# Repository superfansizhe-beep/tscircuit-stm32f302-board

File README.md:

# STM32F302R8T6 考核板 —— 用 TypeScript 画电路

**这是一块完整的 STM32 开发板的全部设计源文件**：原理图、PCB、BOM、
交付产物，以及把 tscircuit（电路即代码）跑起来的钉死工具链。

| | |
|---|---|
| 板子 | **80 × 80 mm，4 层** |
| 主控 | STM32F302R8T6（LQFP-64） |
| 元件 | 84 个（261 SMT 焊盘 + 76 通孔） |
| 原理图 | **9 页**（电源 / 最小系统 / 串口 / I2C / SPI / CAN / PWM / ADC / 指示灯） |
| 走线 | 234 条、197 个过孔 |
| 铜皮 | 内层1 + 底层 GND 平面 |

## 这块板做什么

一块自制的 STM32F302 开发板，把常用外设一次性做全：

- **电源**：XT30 输入 → 拨动开关 → RY8411 降压到 5V → TLV75733 LDO 到 3.3V，三颗电源指示灯
- **最小系统**：8MHz HSE 晶振、复位/启动按键、SWD 调试口、全套去耦
- **外设**：3 路串口（PH2.0）、3 路 I2C（EEPROM + 温度传感器 + 引出）、
  2 路 SPI（MCP23S17 扩 16 路 GPIO + 引出）、1 路 CAN、
  6 路 PWM 舵机轨、3 路 ADC 电源电压采样、3 路 GPIO 指示灯

## 交付产物在哪

[`out/stm32f302/deliverables/`](out/stm32f302/deliverables/) ——
**含 `.epro2` 转换步骤与已知问题，要交作业先看这里的说明。**

| 目录 | 内容 |
|------|------|
| `01-原理图/` | 九页 PDF + 分页 PNG + 矢量 SVG |
| `02-PCB/` | 正反面/全板图 + Gerber（4 层，含内层与钻孔） |
| `03-导入EasyEDA/` | Altium 工程（转 `.epro2` 用）+ KiCad PCB |
| `04-制造资料/` | BOM.csv（37 种料号）+ 网表 |
| `05-3D/` | 整板 STEP 模型 |

## 为什么"电路是代码"

整块板用 TSX 描述（`<chip>` `<resistor>` `<trace>` 这些标签），
而不是画在 EDA 软件里。好处是**可复跑、可 diff、可程序化校验**：

```bash
export PATH="$HOME/Desktop/tscircuit/.tooling/bun/bin:$PATH"
./tsci-run export circuits/stm32f302/main.tsx -f circuit-json -o ../../out/stm32f302/main.json

python3 scripts/check-modules.py   # 元件数 / 丢件 / 几何重叠 / 越出板边
python3 scripts/erc.py             # 八项电气规则（短路 / 重复网络 / 悬空脚 …）
./scripts/render-all.sh            # 刷新全部图片
./scripts/export-deliverables.sh   # 刷新全部交付文件
python3 scripts/gen-bom.py         # 从电路产物反推 BOM
```

**这两个校验脚本不是摆设** —— 它们在开发过程中抓出了 8 个"构建成功但板子是废的"
的错误，比如：晶振缺参数导致元件静默消失、绿/蓝 LED 极性写反、
磁珠料号在库里不存在导致元件零焊盘、网络名与位号重名等等。
逐条记录在 [`circuits/stm32f302/README.md`](circuits/stm32f302/README.md)。

## 目录

| 路径 | 说明 |
|------|------|
| `circuits/stm32f302/` | **本项目**：9 个模块 + 零件库 + 需求/引脚/BOM/位号文档 |
| `circuits/stm32f302/parts/` | 可复用零件（降压块、LDO 块、指示灯、PH2.0 接口、上拉对、分压） |
| `scripts/` | 验收、ERC、BOM 生成、渲染、导出 |
| `out/stm32f302/` | 构建产物与交付文件 |
| 以下 | 宿主环境的工具链契约 |

---

# my-tscircuit —— 基准机 / 环境契约

这是**基准机**，不是 mock。它是钉死的、可复跑的宿主环境：正式的电路项目也住在这里面，
或者整个目录复制一份当模板用。

**环境不可变，复现靠目录快照，而不是靠记忆。**

> 本文档里的命令都是在本目录实测跑出来的，不是照抄文档。
> 标 ⚠️ 的是实测踩到、且和原始契约写法**不一致**的地方。

---

## Toolchain Contract

| # | 契约 | 内容 |
|---|------|------|
| 1 | 运行时 | Bun 1.3.3。用 `tsci-run` wrapper 起；Node 跑会报 `ERR_UNSUPPORTED_DIR_IMPORT`（Node 不允许目录 import，Bun 允许） |
| 2 | 包 | `@tscircuit/cli@0.1.2277` + `tscircuit@0.0.2790`；`package.json` 的 `overrides` 钉死 `@tscircuit/core@0.0.2119` |
| 3 | 源 | `.npmrc` 指 `registry=https://registry.npmjs.org`（npmmirror 同步滞后，取不到钉死版本） |
| 4 | 网络 | `kicad:` / `jlcpcb:` 封装抓取走本地 gost 中继 `127.0.0.1:8118`，由 `bunfig.toml` 的 `preload` wrap `fetch` 注入 |
| 5 | fd | `tsci dev` 需要 > 2048（`ulimit -n 65536`）；沙箱硬顶 2048 时 fallback 到无头 `export` |
| 6 | 补丁 | `patches/@tscircuit%2Fcore@0.0.2119.patch` 由 `bun install` 自动应用，把 core#4481 的诊断修复固化下来（见「本地补丁」） |

### 为什么必须是这个目录，不能全局装

契约里有 4 条只在项目目录内才生效：

| 契约 | 全局做不了的原因 |
|------|------------------|
| `overrides` 钉 core 版本 | `package.json` overrides 是项目级机制，全局装包没法 override 别的包的依赖树 |
| `.npmrc` 指官方源 | 可以全局，但项目级更稳，不受你机器上其他项目切换源影响 |
| `bunfig.toml` preload wrap fetch | preload 配置按项目目录读，只有在这里跑的 bun 命令会加载它 |
| `node_modules` 隔离 | Bun 目录 import 风格的 ESM 只在这个 node_modules 里自洽，扔别的目录下 Node 会炸 |

所以「新文件夹」不是习惯，是这些钉子的唯一挂载点。

### 版本钉子的真实依据

- `@tscircuit/cli@0.1.2277` 本身是**零依赖打包**（`bin: tscircuit-cli`），不直接吃 core；
  真正吃 core 的是 `tscircuit@0.0.2790`，它声明 `@tscircuit/core: ^0.0.2117`。
  caret 会浮动，所以用 `overrides` 钉到具体版本 `0.0.2119`（该包当前的 latest）。
  实测装出来确实是 `0.0.2119`。
- 这类「Cannot find module '@tscircuit/core'」的报错在 tscircuit/cli 的 issue
  #1657 / #3982 有复现（不同 core 版本组合），钉版本是标准解法。
- `ERR_UNSUPPORTED_DIR_IMPORT` 是 Node 的 ESM 目录导入错误，Bun 默认允许 —— 第 1 条契约的由来。

---

## ⚠️ 三处必须偏离原始写法的地方

### 1. 不要用 `bunx --bun @tscircuit/cli`

```bash
# ❌ 不要这样 —— 实测会打印 "Resolved, downloaded and extracted [618]"
bunx --bun @tscircuit/cli export circuits/blink.tsx -f pcb-svg
```

`bunx` 在自己的临时缓存目录里**重新解析整棵依赖树**，完全绕开本项目的
`node_modules` 和 `package.json` 的 `overrides` —— 等于把**第 2 条契约直接作废**，
还会重新触发 sharp 的 install script。

### 2. 也不要直接跑 `node_modules/.bin/tscircuit-cli`

```bash
# ❌ 不要这样
./node_modules/.bin/tscircuit-cli export ...
```

它的 shebang 是 `#!/usr/bin/env node`，直接执行就落到 Node 上 → `ERR_UNSUPPORTED_DIR_IMPORT`。

所以才有 `tsci-run`：它用 `process.execPath`（Bun 自身绝对路径）强制 Bun 运行时，
同时指向**本地那份**钉死的 CLI。两个问题一次解决。

### 3. `-o` 是文件路径，且相对**电路文件所在目录**解析

```bash
# ❌ 会被解析成 circuits/out/ → ENOENT
./tsci-run export circuits/blink.tsx -f pcb-svg -o out/blink.svg

# ✅ 对
./tsci-run export circuits/blink.tsx -f pcb-svg -o ../out/blink.pcb.svg
```

`-o` 要给完整文件名，不能给目录。

---

## 常用命令（已验证可跑）

```bash
cd my-tscircuit

# ⚠️ 必须带 --ignore-scripts
# 实测：不带会因 sharp 的 postinstall 失败而返回非零退出码（CI / set -e 会直接中断）。
# 带了就干净通过（rc=0），且 5 种导出格式与版本钉死全部正常 —— sharp 在本项目里根本用不到。
bun install --frozen-lockfile --ignore-scripts
```

**导出（无头，一次性产物，fd 受限时的 fallback）**

```bash
./tsci-run export circuits/blink.tsx -f readable-netlist -o ../out/blink.netlist.txt
./tsci-run export circuits/blink.tsx -f pcb-svg        -o ../out/blink.pcb.svg
./tsci-run export circuits/blink.tsx -f schematic-svg  -o ../out/blink.schematic.svg
./tsci-run export circuits/blink.tsx -f pcb-png        -o ../out/blink.pcb.png
./tsci-run export circuits/blink.tsx -f gerbers        -o ../out/blink.gerbers.zip
```

实测全部通过。`export --help` 里支持的格式还有：
`json` `circuit-json` `schematic-pdf` `gltf` `glb` `specctra-dsn` `kicad_sch`
`kicad_pcb` `kicad_zip` `altium` `kicad-library` `srj` `step` `assembly-svg`
`component-box-3mf`

**开发服务器（需要 watch + 多 worker，fd 消耗大）**

```bash
ulimit -n 65536                              # macOS 默认偏低，先抬 fd
./tsci-run dev circuits/blink.tsx            # → http://localhost:3020
```

实测 `lsof` 确认监听 `*:3020`，`curl` 返回 200。

`fd` 不够时的取舍：dev 起多 worker + watch，吃 fd；export 是无头单次任务，不受影响。
沙箱 fd 硬顶 2048 时一律退回 export。

---

## 已知问题（不阻塞，但要知道）

### sharp 的 postinstall 会失败 —— 已绕过，不影响任何导出

`sharp@0.32.6` 要从 GitHub release 拉 libvips 预编译包，本机网络拉不下来
（HTTP/2 framing error / ECONNREFUSED / timeout 都遇到过），fallback 去源码编译也失败，
最终 `install script from "sharp" exited with 1`。

**实测影响**：
- `require("sharp")` 会抛「Cannot find module sharp-darwin-arm64v8.node」
- 但 **svg / png / gerbers / netlist 五种导出全部照常**（`pcb-png` 走 resvg，不经 sharp）
- 唯一实际后果：`bun install` 返回**非零退出码**，CI 或 `set -e` 会中断

**已修**：安装命令统一带 `--ignore-scripts`（见「常用命令」），rc=0，且导出全绿。
本项目任何路径都用不到 sharp，跳过所有 install script 是安全的。
真要用 sharp 时再单独 `cd node_modules/sharp && node install/libvips`（前提是网络能通）。

### `-f circuit-json` 会写两份文件

实测：对 `circuits/blink.tsx` 跑 `-f circuit-json -o ../out/check.json`，
除了 `out/check.json`，**还会在电路文件旁多写一份 `circuits/blink.circuit.json`**，
两份内容逐字节相同。

不影响正确性，但会污染源码目录。已在 `.gitignore` 里排除 `circuits/*.circuit.json`。
其他格式（netlist / svg / png / gerbers）实测**不会**有这个问题。

### autorouting 产物存不下来 —— 上游问题，已提 issue + PR

`@tscircuit/core@0.0.2119`（截至 2026-10-09 的 npm latest）会出现：

```
Could not save autorouting paths for subcircuit_source_group_0:
Saved phase path ".LED1 > port.pin1" must end at another connection endpoint;
use autorouter="fanout" for saved escapes
```

**注意：PCB 本身是正确布线的**（无 `pcb_autorouting_error`，`pcb_trace` 都有真实几何和
正确的起止 `pcb_port_id`）。丢的只是 `.tscircuit/autorouting-artifacts/` 那个
可回放产物，CLI 因此跳过写入。严重性：**轻微**，不是渲染缺陷。

**真实根因**（在 core 仓库里逐变量插桩定位到的，比最初的猜测更窄）：saved path 要求
走线两端属于**同一条 SRJ 连接**；而当某个 pin 同时属于两条连接时，路由器会把这条网络
布成一棵**跨连接**的树——经由另一条连接的 port 抵达，而不是直接连线过去。此时无论
锚在哪一端都无法表达，该产物只能作废。

`autorouter="fanout"`（报错自己推荐的解法）实测**一字不变地无效**。

最小复现（`R1.pin2` 同时属于两条连接）：

```tsx
<chip name="U1" footprint="soic8" pinLabels={{ pin1: "VCC", pin2: "GND", pin3: "OUT", pin4: "IN" }} pcbX={0} />
<resistor name="R1" resistance="330" footprint="0402" pcbX={-6} pcbY={0} />
<led name="LED1" footprint="0402" pcbX={6} pcbY={0} />
<trace from="U1.VCC" to="R1.pin1" />
<trace from="U1.OUT" to="R1.pin2" />
<trace from="R1.pin2" to="LED1.pin1" />
<trace from="LED1.pin2" to="U1.GND" />
```

**影响**：`circuits/blink.tsx` 恰好有一个 pin（`R1.pin2`）同时属于两条连接，所以踩到了；
改成串联通路就不会出现。导出本身永远成功，只是那个产物存不下来。

### 相关上游进展（2026-10-09 查）

**已提交**：[issue #4481](https://github.com/tscircuit/core/issues/4481)（已按实测更正根因与严重性）
+ [PR #4482](https://github.com/tscircuit/core/pull/4482) —— 修的是**报错误导性**：
在锚定走线时识别「跨连接」形态，用可读的 port 名报出是哪两个 port，
不再甩锅给一条从未被保存的路径、不再推荐无效的 `autorouter="fanout"`。
（+37 行、0 删除，带 `tests/repros/` 复现测试与 PCB 快照，在 main 上红、修复后绿。）

| 编号 | 状态 | 说明 |
|------|------|------|
| [core#4482](https://github.com/tscircuit/core/pull/4482) | **open（本次提交）** | 让诊断指向真实成因 |
| [core#4481](https://github.com/tscircuit/core/issues/4481) | open（本次提交） | 问题报告，含最小复现与隔离表 |
| [core#4197](https://github.com/tscircuit/core/issues/4197) | 已关闭 | 同一句报错的出处，由 [#4204](https://github.com/tscircuit/core/pull/4204) 修复且**确实包含在 0.0.2119 里**（compare `7f68819...abe48513` = ahead 239 / behind 0）。但本条是**另一个成因**（跨连接走线），不是那个修复的残留缺口 |
| [core#3887](https://github.com/tscircuit/core/issues/3887) | 已关闭 | 症状同为 `undefined connectedPort.x`，但触发条件是**异步/文件加载的 `.kicad_mod` 封装**缺 `pcb_port_id`，由 #3889/#3892 修复。与本条不是同一路径 |
| [core#4337](https://github.com/tscircuit/core/pull/4337) | open | repro：对角封装铜箔 abort autorouting。相邻但不同 |
| [core#4477](https://github.com/tscircuit/core/pull/4477) | open | fix：保留手动 `pcbPath`。相邻但不同 |
| [core#4192](https://github.com/tscircuit/core/pull/4192) | open | fix：忽略无主顶层走线。相邻但不同 |

搜 `connectedPort`、`must end at another connection endpoint`、`getSimpleRouteJson`
在 open issue / PR 里**均 0 命中** —— 提交时没有任何 PR 在正面修这条。

**规避办法**：设计电路时避免让同一个 pin 同时属于两条连接（串联化即可），
否则该板的 autorouting 产物存不下来；PCB 渲染不受影响。
上游若改成「按电气网络合并成一条多端连接」就能真正存下来，
但那属于建模改动，需要维护者定夺。届时改 `overrides` 里的版本号即可。

---

## 本地补丁（patches/）

上游 PR [#4482](https://github.com/tscircuit/core/pull/4482) 的修复已经**用 `bun patch` 固化成
本项目的第 6 条契约**，不需要等上游合并：

```
patches/@tscircuit%2Fcore@0.0.2119.patch   # 改的是 core 打包产物的 dist/index.js
package.json → patchedDependencies
```

`bun install` 会**自动**应用它，无需任何手工步骤。实测全新安装 rc=0，
补丁自动生效，五种导出全绿。

**为什么需要它**：不打补丁时导出每条分支拓扑电路都会打印
`Saved phase path "..." must end at another connection endpoint; use autorouter="fanout" for saved escapes`
—— 甩锅给一条从未被保存的路径，还推荐一个实测无效的解法。打上补丁后变成：

```
Route between .LED1 > port.pin1 and .U1 > port.OUT spans separate connections of
the same net; the router reached one port through the other instead of tracing
between them, which a saved path cannot express
```

**验证补丁是否生效**：

```bash
grep -c "spans separate connections" node_modules/@tscircuit/core/dist/index.js   # 1 = 已打上
```

**⚠️ 补丁绑死版本号**。key 是 `@tscircuit/core@0.0.2119`，和 `overrides` 一致。
上游修好后升级 core，补丁会失效（bun 不会把 0.0.2119 的补丁套到新版本上），这时应该：

```bash
# 1. 删掉 package.json 的 patchedDependencies
# 2. 删掉 patches/ 目录
# 3. 改 overrides 里的 core 版本号，重装
```

**补丁没改行为，只改诊断**：跳连接形态下产物依然存不下来（模型层限制，
见下方「autorouting 产物存不下来」），但现在报错说的是真话。

```
my-tscircuit/
├── package.json        # 钉版本 + overrides + patchedDependencies —— 契约的核心
├── bun.lock            # 已生成，换机用 --frozen-lockfile 复现
├── .npmrc              # registry=https://registry.npmjs.org
├── bunfig.toml         # preload = ["./scripts/proxy-fetch.ts"]
├── patches/            # bun patch 产出的本地补丁（install 时自动应用）
│   └── @tscircuit%2Fcore@0.0.2119.patch
├── scripts/
│   └── proxy-fetch.ts  # wrap fetch → 127.0.0.1:8118（解决 kicad:/jlcpcb: 直连 407）
├── tsci-run            # 自建 wrapper，#!/usr/bin/env bun，强制 Bun + 走本地钉死依赖
├── proxy-run           # 启动本地 gost 中继（127.0.0.1:8118）
├── circuits/           # 实际电路 .tsx 都放这
└── out/                # export 产物（netlist / pcb-svg / pcb-png / gerbers...）
```

## 代理调试

### gost 已安装并验证生效

`gost 3.3.0`（Homebrew，`/opt/homebrew/bin/gost`）。启动：

```bash
./proxy-run                    # 前台启动 gost 中继 127.0.0.1:8118
```

**⚠️ 不要用 `brew services start gost`**：Homebrew 默认配置 `/opt/homebrew/etc/gost.yml`
监听的是 `:8080` 且绑 `eth0`，与本契约要求的 `127.0.0.1:8118` 不符。

**自检三连**：

```bash
# 1. 端口在听
lsof -nP -iTCP:8118 -sTCP:LISTEN

# 2. 代理本身通（期望 200）
curl -x http://127.0.0.1:8118 https://easyeda.com/ -o /dev/null -w '%{http_code}\n'

# 3. preload 真的把上游域名送进了代理（而不是回退直连）
TSC_PROXY_DEBUG=1 ./tsci-run export circuits/blink.tsx -f readable-netlist -o ../out/x.txt
```

**实测（2026-10-10，冷缓存）**：清空 `.tscircuit` 后导出，
`jlcsearch.tscircuit.com` 与 `easyeda.com` 全部标记「经代理」，
gost 日志出现真实隧道与字节数，**无「代理失败，回退直连」**。

域隔离也验证过（这是这层 preload 存在的全部理由）：

| 目标 | 走向 | gost 连接记录 |
|---|---|---|
| `registry.npmjs.org` | **直连** | 无 |
| `jlcsearch.tscircuit.com` | 经代理 | 有 |
| `easyeda.com` | 经代理 | 有 |
| `127.0.0.1`（本地） | 直连 | 无 |

### preload 行为

`scripts/proxy-fetch.ts` 只对 `kicad|jlc|lcsc|easyeda|oshwlab` 命中的域名生效，
loopback 一律直连，**代理不通会自动回退原始 fetch**。

```bash
TSC_PROXY_DEBUG=1 ./tsci-run export circuits/blink.tsx -f pcb-svg -o ../out/blink.pcb.svg
TSC_PROXY_ALL=1   ...   # 全部外部请求走代理
TSC_PROXY_OFF=1   ...   # 完全直连（排查代理本身的问题）
```

实测行为（本地起了个最小代理对照验证）：

| 目标 | 行为 |
|------|------|
| `https://easyeda.com/...` | 经代理，CONNECT 隧道通 |
| `https://registry.npmjs.org/...` | **直连**，域名不在匹配范围内 |
| `http://127.0.0.1:...` | 直连，loopback 排除 |
| 代理没起 | 自动回退直连，导出照常成功 |

### ⚠️ 实现要点：用 Bun 原生 `proxy` 选项，不要手写 CONNECT

最初按 oven-sh/bun#30381 的思路在 preload 里手写 `node:http` 的 CONNECT 隧道，
**在 Bun 1.3.3 上根本跑不通**：Bun 的 `node:http` polyfill 不接受 absolute-URI 请求目标，
连 `method: "CONNECT"` 都直接抛 `TypeError: fetch() URL is invalid`。

实测可行的做法是直接用 Bun 原生 fetch 的 `proxy` 选项（CONNECT 隧道已验证可用）：

```ts
originalFetch(input, { ...init, proxy: "http://127.0.0.1:8118" })
```

preload 这层包装依然必要，但理由变了：**它不是为了绕开 Bun 的 CONNECT bug，
而是为了把代理范围限定在 kicad/jlcpcb 上游域名上** —— `HTTP_PROXY` 环境变量是进程级的，
会把 registry.npmjs.org 也一起拐进代理，而 registry 直连才是我们要的。

## 什么时候才需要第二个文件夹

只有一种情况：新项目需要另一套钉死的版本组合（比如 CLI 出大版本、你想 A/B 对比）。
届时不是升级 `my-tscircuit`，而是**整个目录复制一份改版本号**。

## 换机复现

```bash
# 1. 机器上装 Bun 1.3.3
curl -fsSL https://bun.sh/install | bash -s "bun-v1.3.3"

# 2. 拷贝本目录（node_modules/ 已在 .gitignore 里，不带；bun.lock 要带）
# 3. 在目录内落地契约
cd my-tscircuit
bun install --frozen-lockfile --ignore-scripts   # rc=0，逐字节一致的依赖树
                                                  # --ignore-scripts 必须带，见 sharp 一节

# 4. 验证：五种格式 + dev 都要能跑
./tsci-run export circuits/blink.tsx -f pcb-svg -o ../out/blink.pcb.svg
./tsci-run dev circuits/blink.tsx                  # → http://localhost:3020

# 5. 启动本地代理中继（契约第 4 条）
./proxy-run                    # gost 127.0.0.1:8118，前台运行
# 自检：curl -x http://127.0.0.1:8118 https://easyeda.com/ -o /dev/null -w '%{http_code}\n'
```

> **gost 的装法**：`brew install gost`（3.3.0）。
> 这台机器从 GitHub release 直连下不动（HTTP/2 framing error 反复出现，16MB 的 v3
> tar.gz 试了 5 次没下完，v2 的 5MB 也失败），Homebrew 走 ghcr.io bottle 才稳定。

`bun.lock` 已生成并纳入版本管理，`--frozen-lockfile` 比光靠 `package.json` 的版本号更硬。

> **Bun 装在工作区外层**：`../.tooling/bun/bin/bun`（1.3.3，macOS arm64），
> 没有动全局环境。要用就把该目录加进 PATH：
> `export PATH="$HOME/Desktop/tscircuit/.tooling/bun/bin:$PATH"`
> 换成 `~/.bun/bin/bun` 全局安装后，`tsci-run` 依然工作（它用 `process.execPath` 取运行时）。

## 工作区位置

```
~/Desktop/tscircuit/            ← tscircuit 专属工作区
├── .tooling/bun/bin/bun       ← Bun 1.3.3（项目外的工具层）
├── my-tscircuit/              ← 本项目（你现在在这）
└── my-tscircuit-baseline.zip  ← 本项目的快照包
```

`.tooling` 与 `my-tscircuit/` 同级，所以 README 里所有 `../.tooling/...` 的
相对引用在任何机器上都成立——**复制整个 `tscircuit/` 目录到别处也能直接用**，
不用改任何路径。换新项目时同理：再复制一份目录、改版本号即可。

---

## 环境健康状态（2026-10-10 实测）

| 项 | 状态 |
|---|---|
| 冷启动（清空 `.tscircuit` 缓存） | ✅ 五种格式全部导出成功，footprint 直接解析 |
| 锁文件复现（`--frozen-lockfile --ignore-scripts`） | ✅ rc=0，版本钉死正确，五种格式全绿 |
| 本地补丁自动应用 | ✅ 全新安装后 `grep -c "spans separate connections"` = 1 |
| 版本钉死 | ✅ core 0.0.2119 / cli 0.1.2277 / tscircuit 0.0.2790 |
| `dev` 服务器 | ✅ 监听 `*:3020`，HTTP 200 |
| `sharp` | ⚠️ 不可用，但被 `--ignore-scripts` 绕过，五种导出不受影响 |
| gost 代理 | ✅ **已装 3.3.0 并实测生效**；冷缓存导出确认上游域名走代理、registry 直连 |
| autorouting 产物 | ⚠️ 分支拓扑下仍存不下来（模型层限制）；**报错已是准确文案**（补丁生效） |

**结论**：日常导出与开发服务器稳定可用，六条契约全部落地且可复现。
唯一剩余缺口是 autorouting 产物本身存不下来（上游建模问题），
但不再报错误导；真正解决要等 core#4481 合并后改 `overrides` 版本号，
届时删掉 `patches/` 即可。

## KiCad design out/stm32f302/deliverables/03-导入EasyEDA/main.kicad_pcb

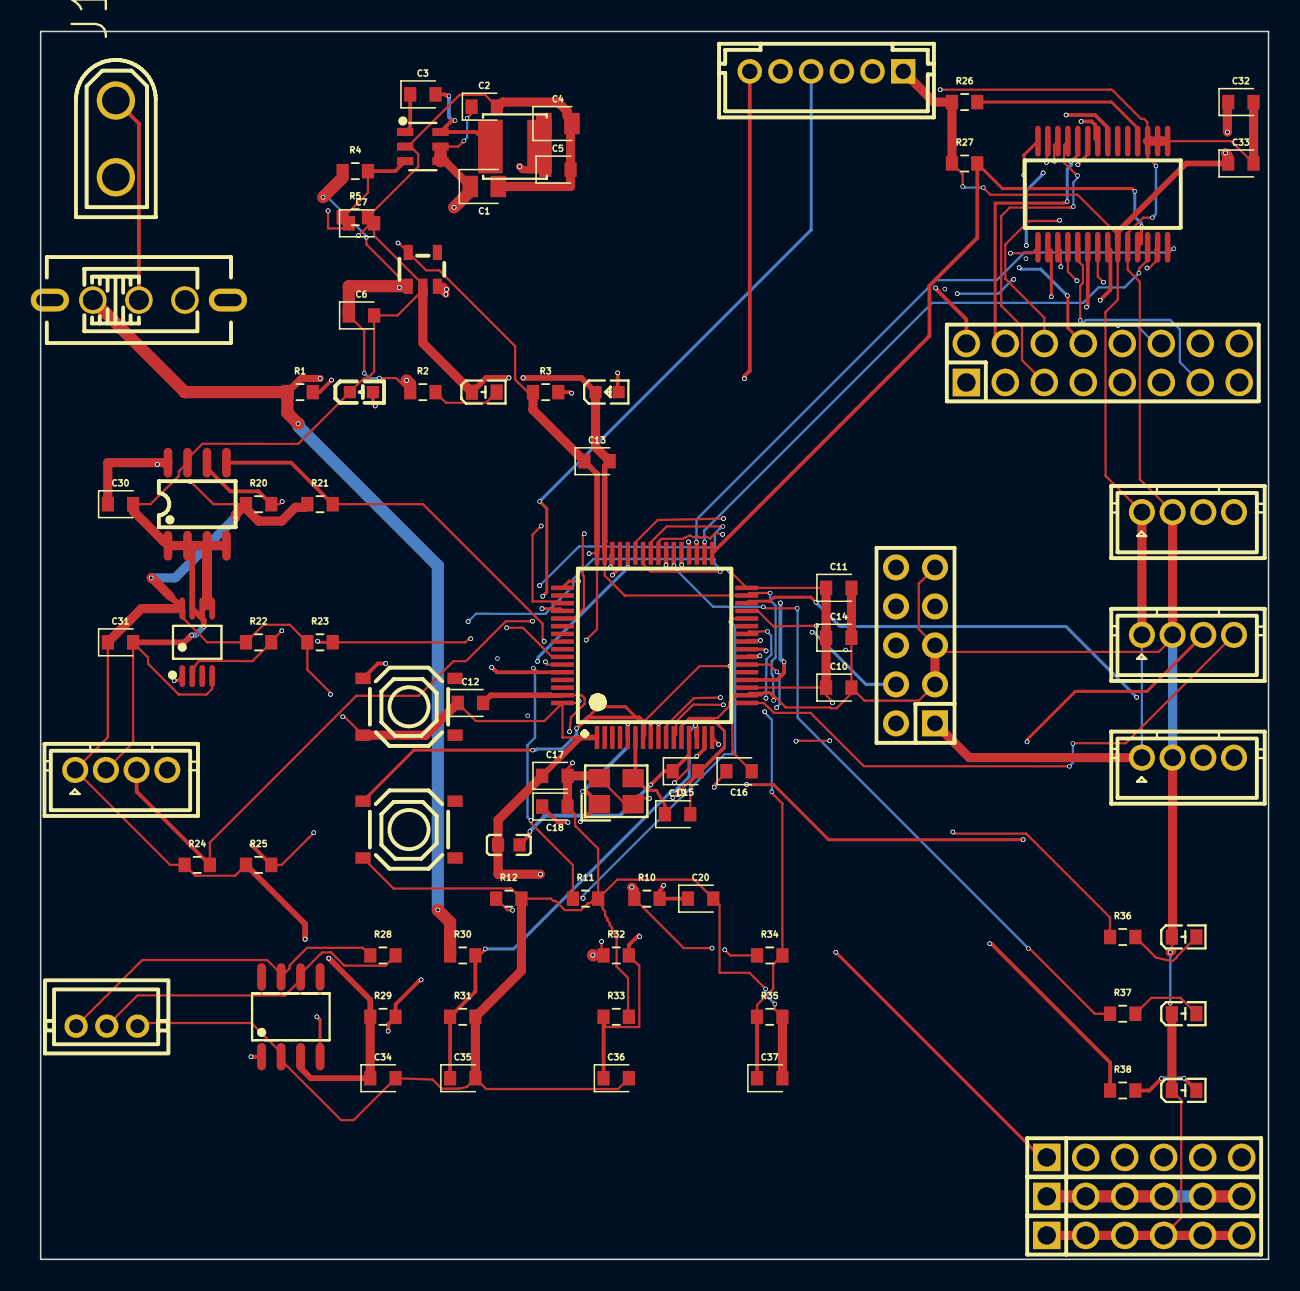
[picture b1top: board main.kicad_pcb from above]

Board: 4 copper layers, 80.0 x 80.0 mm, 84 parts (0 on the bottom side), 75 nets.

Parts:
C1, C4: 22uF; CL21A226MAQNNNE
C2, C3, C5, C10, C11, C12, C13, C17, C20, C30, C31, C32, C33, C34, C35, C36, C37: 100nF; CC0603KRX7R9BB104
C6, C7, C15: 1uF; CL10A105KB8NNNC
C14: 4.7uF; CL10A475KO8NNNC
C16: 10nF; CL10B103KB8NNNC
C18, C19: 12pF; CC0603JRNPO9BN120
D1: KT-0603R
D2: NCD0603G1
D3: NCD0603B1
FB1: BLM18AG601SN1D
J1: J1; XT30UPB-M
J2: J2; WAFER-PH2_0-4PZZ
J3: J3; WAFER-PH2_0-4PZZ
J4: J4; WAFER-PH2_0-4PZZ
J5: J5; WAFER-PH2_0-4PZZ
J6: J6; WAFER-PH2_0-6PZZ
J7: J7; WAFER-PH2_0-3PZZ
J8: J8; 2_54-1x6P
J9: J9; 2_54-1x6P
J10: J10; 2_54-1x6P
J11: J11; PZ2_54-2X5P-H25
J12: J12; 2_54-2_8P
L1: 4.7µH; CKCSA4020-4_7uH_M
LED1, LED2, LED3: NCD0603G1
R1, R20, R21, R22, R23, R24, R25: 4.7kΩ; 0603WAF4701T5E
R2, R36, R37, R38: 1kΩ; 0603WAF1001T5E
R3: 330Ω; 0603WAF3300T5E
R4, R30, R32, R33: 100kΩ; 0603WAF1003T5E
R5: 19.1kΩ; 0603WAF1912T5E
R10, R11, R12, R26, R27, R29, R34: 10kΩ; 0603WAF1002T5E
R28: 120Ω; 0603WAF1200T5E
R31: 27kΩ; 0603WAF2702T5E
R35: 33kΩ; 0603WAF3302T5E
SW1: SS-12F44-G5
SW2, SW3: TS-1187A-B-A-B
U1: RY8411
U2: TLV75733PDBVR
U3: STM32F302R8T6
U4: AT24C64D-SSHM-T
U5: TMP1075DGKR
U6: MCP23S17T-E/SS; MCP23S17T-E_SS
U7: TCAN332DR
Y1: Y1; TAXM8M4RDBCCT2T

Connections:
ADC_3V3: C37.1, R34.2, R35.1, U3.26
ADC_5V: C36.1, R32.2, R33.1, U3.15
ADC_12V: C35.1, R30.2, R31.1, U3.14
BOOT0: R11.1, SW3.1, U3.60
CANH: J7.1, R28.1, U7.7
CANL: J7.2, R28.2, U7.6
CAN_RX: U3.44, U7.4
CAN_TX: R29.2, U3.45, U7.1
FB: R4.2, R5.1, U1.3
GND: C1.2, C2.2, C4.2, C5.2, C6.2, C7.2, C10.2, C11.2, C12.2, C13.2, C14.2, C15.2, C16.2, C17.2, C18.2, C19.2, C20.2, C30.2, C31.2, C32.2, C33.2, C34.2, C35.2, C36.2, C37.2, D1.2, D2.1, D3.1, J1.2, J2.2, J3.2, J4.2, J5.2, J6.2, J7.3, J10.1, J10.2, J10.3, J10.4, J10.5, J10.6, J11.3, J11.5, J11.9, LED1.1, LED2.1, LED3.1, R5.2, R11.2, R12.2, R31.2, R33.2, R35.2, SW2.3, U1.2, U2.2, U3.12, U3.18, U3.31, U3.47, U3.63, U4.1, U4.2, U4.3, U4.4, U4.7, U5.4, U5.5, U5.6, U5.7, U6.10, U6.15, U6.16, U6.17, U7.2, Y1.2, Y1.4
GPIO_LED1: R36.1, U3.37
GPIO_LED2: R37.1, U3.38
GPIO_LED3: R38.1, U3.39
HSE_IN: C18.1, U3.5, Y1.1
HSE_OUT: C19.1, U3.6, Y1.3
I2C1_SCL: R20.2, U3.58, U4.6
I2C1_SDA: R21.2, U3.59, U4.5
I2C2_SCL: R22.2, U3.42, U5.2
I2C2_SDA: R23.2, U3.43, U5.1
I2C3_SCL: J5.3, R24.2, U3.41
I2C3_SDA: J5.4, R25.2, U3.40
J1.VIN to SW1.COM: J1.1, SW1.2
MCP_RESET: R26.2, U6.18
NRST: C20.1, J11.10, R10.2, SW2.1, U3.7
PWM1: J8.1, U3.8
PWM2: J8.2, U3.9
PWM3: J8.3, U3.10
PWM4: J8.4, U3.11
PWM5: J8.5, U3.22
PWM6: J8.6, U3.23
R1.pin2 to D1.anode: D1.1, R1.2
R2.pin2 to D2.anode: D2.2, R2.2
R3.pin2 to D3.anode: D3.2, R3.2
R12.pin1 to U3.pin28: R12.1, U3.28
R36.pin2 to LED1.anode: LED1.2, R36.2
R37.pin2 to LED2.anode: LED2.2, R37.2
R38.pin2 to LED3.anode: LED3.2, R38.2
SPI2_CS: R27.2, U3.33, U6.11
SPI2_MISO: U3.35, U6.14
SPI2_MOSI: U3.36, U6.13
SPI2_SCK: U3.34, U6.12
SPI3_CS: J6.6, U3.20
SPI3_MISO: J6.4, U3.52
SPI3_MOSI: J6.5, U3.53
SPI3_SCK: J6.3, U3.51
SW: C3.2, L1.1, U1.6
SWCLK: J11.4, U3.49
SWDIO: J11.2, U3.46
U1.BS to C3.pin1: C3.1, U1.1
U6.GPA0 to J12.pin1: J12.1, U6.21
U6.GPA1 to J12.pin2: J12.2, U6.22
U6.GPA2 to J12.pin3: J12.3, U6.23
U6.GPA3 to J12.pin4: J12.4, U6.24
U6.GPA4 to J12.pin5: J12.5, U6.25
U6.GPA5 to J12.pin6: J12.6, U6.26
U6.GPA6 to J12.pin7: J12.7, U6.27
U6.GPA7 to J12.pin8: J12.8, U6.28
U6.GPB0 to J12.pin9: J12.9, U6.1
U6.GPB1 to J12.pin10: J12.10, U6.2
U6.GPB2 to J12.pin11: J12.11, U6.3
U6.GPB3 to J12.pin12: J12.12, U6.4
U6.GPB4 to J12.pin13: J12.13, U6.5
U6.GPB5 to J12.pin14: J12.14, U6.6
U6.GPB6 to J12.pin15: J12.15, U6.7
U6.GPB7 to J12.pin16: J12.16, U6.8
UART1_RX: J2.4, U3.25
UART1_TX: J2.3, U3.24
UART2_RX: J3.4, U3.17
UART2_TX: J3.3, U3.16
UART3_RX: J4.4, U3.30
UART3_TX: J4.3, U3.29
V3_3: C7.1, C10.1, C11.1, C12.1, C13.1, C14.1, C17.1, C30.1, C31.1, C32.1, C33.1, C34.1, FB1.1, J2.1, J3.1, J4.1, J5.1, J6.1, J11.1, R3.1, R10.1, R20.1, R21.1, R22.1, R23.1, R24.1, R25.1, R26.1, R27.1, R29.1, R34.1, SW3.3, U2.5, U3.1, U3.19, U3.32, U3.48, U3.64, U4.8, U5.8, U6.9, U7.3
V5: C4.1, C5.1, C6.1, J9.1, J9.2, J9.3, J9.4, J9.5, J9.6, L1.2, R2.1, R4.1, R32.1, U2.1, U2.3
V12: C1.1, C2.1, R1.1, R30.1, SW1.1, U1.4, U1.5
VDDA: C15.1, C16.1, FB1.2, U3.13

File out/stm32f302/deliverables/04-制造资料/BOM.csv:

序号,C编号,厂商型号,封装,参数,数量,位号
1,C14663,CC0603KRX7R9BB104,0603,100nF,17,C2 C3 C5 C10 C11 C12 C13 C17 C20 C30 C31 C32 C33 C34 C35 …
2,C23162,0603WAF4701T5E,0603,4.7kΩ,7,R1 R20 R21 R22 R23 R24 R25
3,C25804,0603WAF1002T5E,0603,10kΩ,7,R10 R11 R12 R26 R27 R29 R34
4,C21190,0603WAF1001T5E,0603,1kΩ,4,R2 R36 R37 R38
5,C25803,0603WAF1003T5E,0603,100kΩ,4,R4 R30 R32 R33
6,C5359601,WAFER-PH2.0-4PZZ,"Plugin,P=2mm",—,4,J2 J3 J4 J5
7,C84267,NCD0603G1,0603,green,4,D2 LED1 LED2 LED3
8,C15849,CL10A105KB8NNNC,0603,1uF,3,C6 C7 C15
9,C37208,2.54-1x6P,"Plugin,P=2.54mm",—,3,J10 J8 J9
10,C107034,CC0603JRNPO9BN120,0603,12pF,2,C18 C19
11,C318884,TS-1187A-B-A-B,"SMD-4P,5.1x5.1mm",—,2,SW2 SW3
12,C45783,CL21A226MAQNNNE,0805,22uF,2,C1 C4
13,C128577,MCP23S17T-E/SS,SSOP-28-208mil,—,1,U6
14,C136718,SS-12F44-G5,Plugin,—,1,SW1
15,C1589,CL10B103KB8NNNC,0603,10nF,1,C16
16,C19330,BLM18AG601SN1D,0603,—,1,FB1
17,C19666,CL10A475KO8NNNC,0603,4.7uF,1,C14
18,C22787,0603WAF1200T5E,0603,120Ω,1,R28
19,C2286,KT-0603R,0603,red,1,D1
20,C22897,0603WAF1912T5E,0603,19.1kΩ,1,R5
21,C22967,0603WAF2702T5E,0603,27kΩ,1,R31
22,C23138,0603WAF3300T5E,0603,330Ω,1,R3
23,C2864807,TMP1075DGKR,VSSOP-8,—,1,U5
24,C2935411,RY8411,SOT-23-6,—,1,U1
25,C354583,CKCSA4020-4.7uH/M,"SMD,4x4mm",4.7µH,1,L1
26,C400090,TAXM8M4RDBCCT2T,SMD3225-4P,8MHz,1,Y1
27,C4216,0603WAF3302T5E,0603,33kΩ,1,R35
28,C42431818,PZ2.54-2X5P-H25,"Plugin,P=2.54mm",—,1,J11
29,C428721,XT30UPB-M,插件通孔（XT30 板端公头）,—,1,J1
30,C485517,TLV75733PDBVR,SOT-23-5,—,1,U2
31,C504601,STM32F302R8T6,LQFP-64(10x10),—,1,U3
32,C5359600,WAFER-PH2.0-3PZZ,"Plugin,P=2mm",—,1,J7
33,C5359603,WAFER-PH2.0-6PZZ,"Plugin,P=2mm",—,1,J6
34,C6487,AT24C64D-SSHM-T,SOIC-8,—,1,U4
35,C68234,2.54-2*8P,"Plugin,P=2.54mm",—,1,J12
36,C73651,TCAN332DR,SOIC-8,—,1,U7
37,C84266,NCD0603B1,0603,blue,1,D3
